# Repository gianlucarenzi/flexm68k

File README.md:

# flexm68k

This is a Proof Of Concept to relocate anywhere in the motherboard of an Amiga500 the CPU.
It consists of two PCB Adapter for Original Primary CPU Socket Adapter + a 64pin FFC/FPC cable and a Secondary CPU Socket Adapter with the add of power supply (as seen in the Molex Floppy Header Power Cable)

Will it work?? ;-P

Gianluca

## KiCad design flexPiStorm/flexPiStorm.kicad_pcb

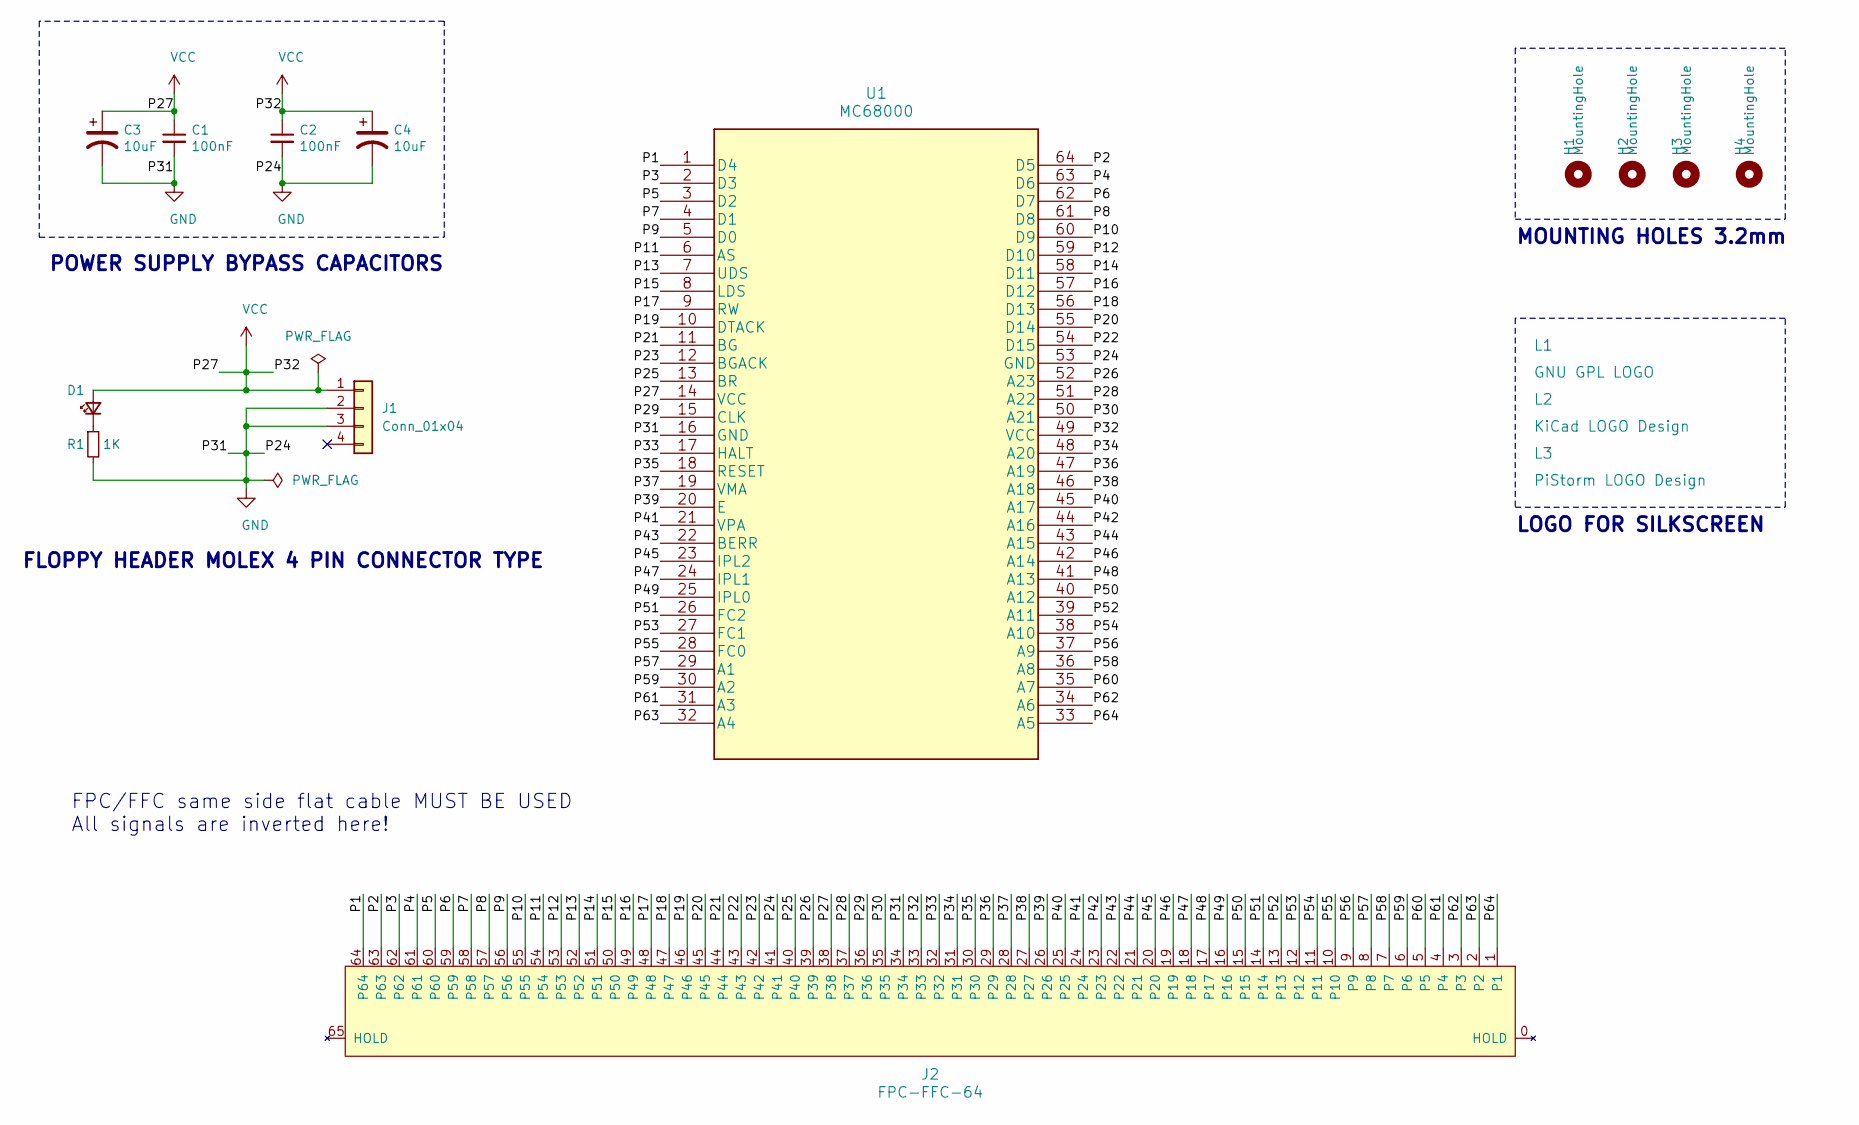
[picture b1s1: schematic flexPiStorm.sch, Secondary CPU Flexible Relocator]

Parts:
C1, C2: 100nF; C_1206_3216Metric_Pad1.33x1.80mm_HandSolder
C3, C4: 10uF; CP_EIA-3216-12_Kemet-S_Pad1.58x1.35mm_HandSolder
D1: LED_Small; LED_1206_3216Metric_Pad1.42x1.75mm_HandSolder
H1, H2, H3, H4: MountingHole; MountingHole_3.2mm_M3
J1: Conn_01x04; PinHeader_1x04_P2.54mm_Horizontal
J2: FPC-FFC-64; FPC_64
L1: GNU GPL LOGO; Symbol_GNU-GPL_SilkScreen_Small
L2: KiCad LOGO Design; KiCad-Logo2_6mm_SilkScreen
L3: PiStorm LOGO Design; PiStorm_32x6-NEG
R1: 1K; R_1206_3216Metric_Pad1.30x1.75mm_HandSolder
U1: MC68000; MC68000-SOCKET-RELOCATOR_FEMALE

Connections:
/P1: J2.64, U1.1 (D4)
/P2: J2.63, U1.64 (D5)
/P3: J2.62, U1.2 (D3)
/P4: J2.61, U1.63 (D6)
/P5: J2.60, U1.3 (D2)
/P6: J2.59, U1.62 (D7)
/P7: J2.58, U1.4 (D1)
/P8: J2.57, U1.61 (D8)
/P9: J2.56, U1.5 (D0)
/P10: J2.55, U1.60 (D9)
/P11: J2.54, U1.6 (AS)
/P12: J2.53, U1.59 (D10)
/P13: J2.52, U1.7 (UDS)
/P14: J2.51, U1.58 (D11)
/P15: J2.50, U1.8 (LDS)
/P16: J2.49, U1.57 (D12)
/P17: J2.48, U1.9 (RW)
/P18: J2.47, U1.56 (D13)
/P19: J2.46, U1.10 (DTACK)
/P20: J2.45, U1.55 (D14)
/P21: J2.44, U1.11 (BG)
/P22: J2.43, U1.54 (D15)
/P23: J2.42, U1.12 (BGACK)
/P25: J2.40, U1.13 (BR)
/P26: J2.39, U1.52 (A23)
/P28: J2.37, U1.51 (A22)
/P29: J2.36, U1.15 (CLK)
/P30: J2.35, U1.50 (A21)
/P33: J2.32, U1.17 (HALT)
/P34: J2.31, U1.48 (A20)
/P35: J2.30, U1.18 (RESET)
/P36: J2.29, U1.47 (A19)
/P37: J2.28, U1.19 (VMA)
/P38: J2.27, U1.46 (A18)
/P39: J2.26, U1.20 (E)
/P40: J2.25, U1.45 (A17)
/P41: J2.24, U1.21 (VPA)
/P42: J2.23, U1.44 (A16)
/P43: J2.22, U1.22 (BERR)
/P44: J2.21, U1.43 (A15)
/P45: J2.20, U1.23 (IPL2)
/P46: J2.19, U1.42 (A14)
/P47: J2.18, U1.24 (IPL1)
/P48: J2.17, U1.41 (A13)
/P49: J2.16, U1.25 (IPL0)
/P50: J2.15, U1.40 (A12)
/P51: J2.14, U1.26 (FC2)
/P52: J2.13, U1.39 (A11)
/P53: J2.12, U1.27 (FC1)
/P54: J2.11, U1.38 (A10)
/P55: J2.10, U1.28 (FC0)
/P56: J2.9, U1.37 (A9)
/P57: J2.8, U1.29 (A1)
/P58: J2.7, U1.36 (A8)
/P59: J2.6, U1.30 (A2)
/P60: J2.5, U1.35 (A7)
/P61: J2.4, U1.31 (A3)
/P62: J2.3, U1.34 (A6)
/P63: J2.2, U1.32 (A4)
/P64: J2.1, U1.33 (A5)
GND: C1.2, C2.2, C3.2, C4.2, J1.2, J1.3, J2.34, J2.41, R1.2, U1.16 (GND), U1.53 (GND)
unnamed: D1.1 (K), R1.1
VCC: C1.1, C2.1, C3.1, C4.1, D1.2 (A), J1.1, J2.33, J2.38, U1.14 (VCC), U1.49 (VCC)

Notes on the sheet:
MOUNTING HOLES 3.2mm
LOGO FOR SILKSCREEN
FLOPPY HEADER MOLEX 4 PIN CONNECTOR TYPE
POWER SUPPLY BYPASS CAPACITORS
FPC/FFC same side flat cable MUST BE USED All signals are inverted here!

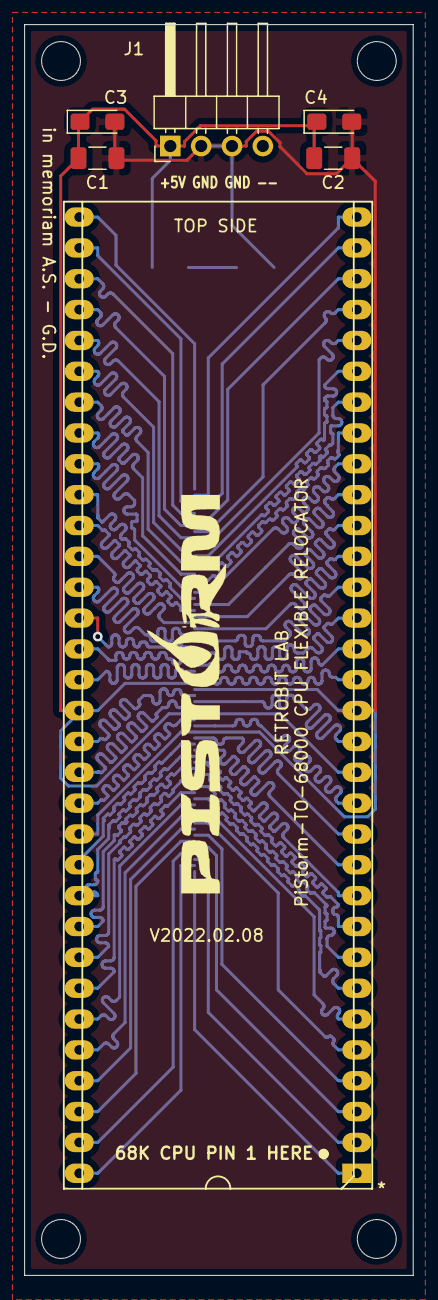
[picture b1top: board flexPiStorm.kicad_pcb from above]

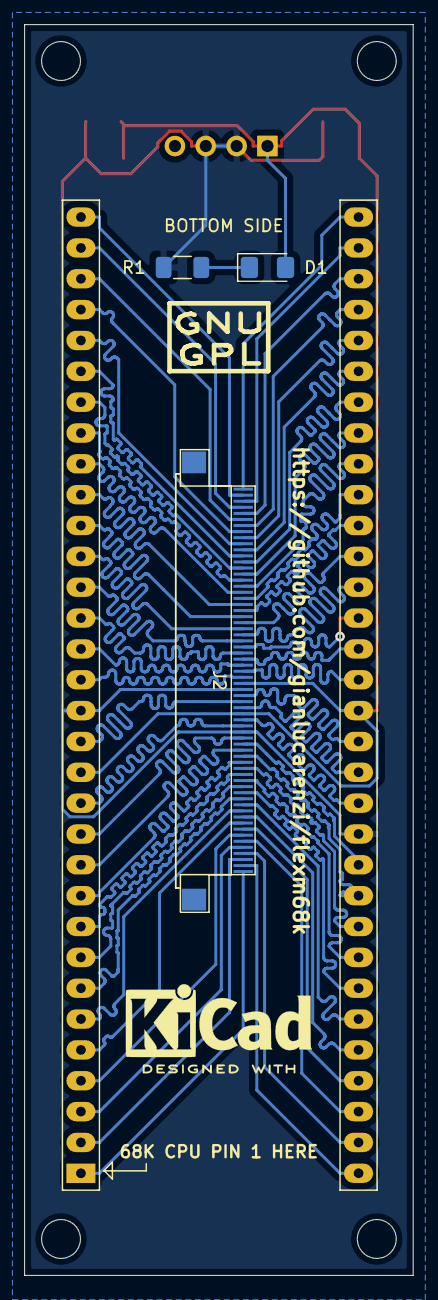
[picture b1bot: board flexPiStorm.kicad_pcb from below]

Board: 2 copper layers, 32.0 x 103.0 mm, 16 parts (5 on the bottom side), 63 nets.

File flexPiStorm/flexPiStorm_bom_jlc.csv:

"Comment","Designator","Footprint","LCSC Part #"
"MC68000","U1","",""
"Conn_01x04","J1","",""
"PiStorm LOGO Design","L3","",""
"100nF","C1 C2","",""
"10uF","C3 C4","",""
"FPC-FFC-64","J2","",""
"LED_Small","D1","",""
"1K","R1","",""
"GNU GPL LOGO","L1","",""
"KiCad LOGO Design","L2","",""

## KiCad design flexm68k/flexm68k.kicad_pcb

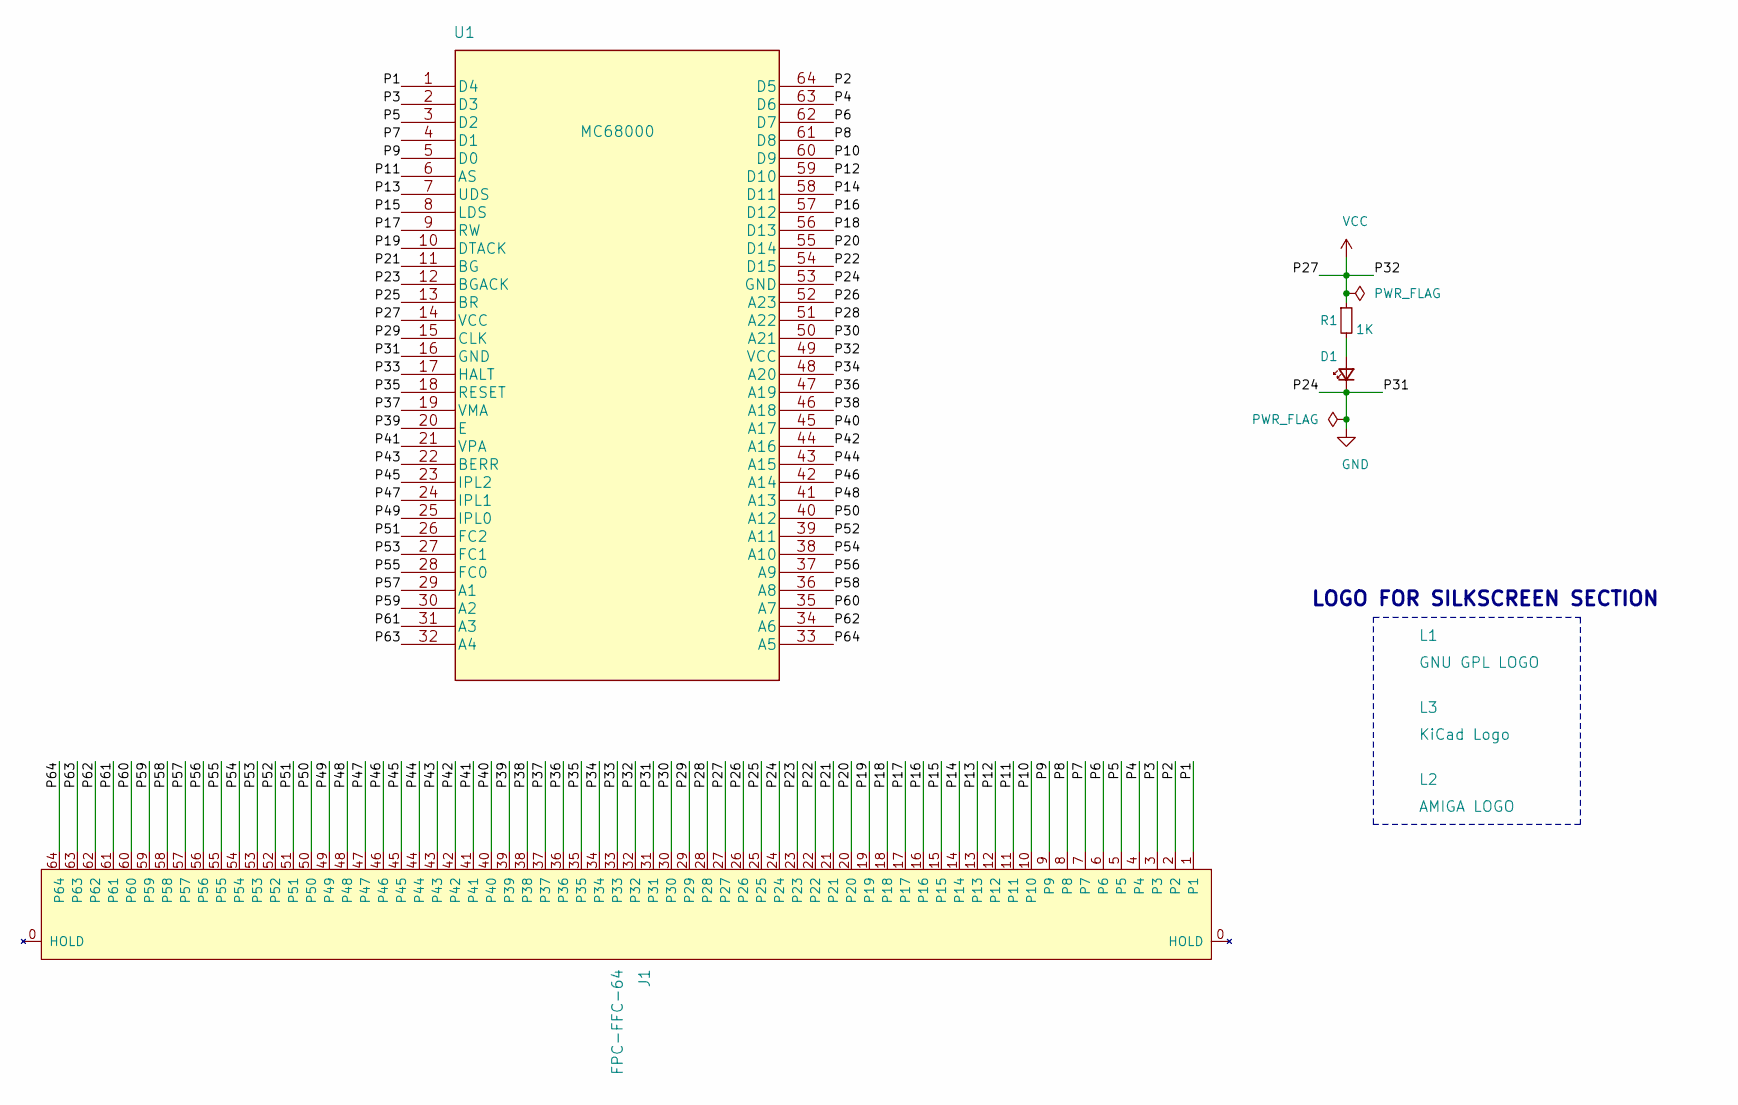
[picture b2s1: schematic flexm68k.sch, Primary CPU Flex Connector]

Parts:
D1: LED_Small; LED_1206_3216Metric_Pad1.42x1.75mm_HandSolder
J1: FPC-FFC-64; FPC_64
L1: GNU GPL LOGO; Symbol_GNU-GPL_SilkScreen_Small
L2: AMIGA LOGO; amigaLogo_BW_31x12mm
L3: KiCad Logo; KiCad-Logo2_6mm_SilkScreen
R1: 1K; R_1206_3216Metric_Pad1.30x1.75mm_HandSolder
U1: MC68000; MC68000-RELOCATOR-MALE

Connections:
/P1: J1.1, U1.1 (D4)
/P2: J1.2, U1.64 (D5)
/P3: J1.3, U1.2 (D3)
/P4: J1.4, U1.63 (D6)
/P5: J1.5, U1.3 (D2)
/P6: J1.6, U1.62 (D7)
/P7: J1.7, U1.4 (D1)
/P8: J1.8, U1.61 (D8)
/P9: J1.9, U1.5 (D0)
/P10: J1.10, U1.60 (D9)
/P11: J1.11, U1.6 (AS)
/P12: J1.12, U1.59 (D10)
/P13: J1.13, U1.7 (UDS)
/P14: J1.14, U1.58 (D11)
/P15: J1.15, U1.8 (LDS)
/P16: J1.16, U1.57 (D12)
/P17: J1.17, U1.9 (RW)
/P18: J1.18, U1.56 (D13)
/P19: J1.19, U1.10 (DTACK)
/P20: J1.20, U1.55 (D14)
/P21: J1.21, U1.11 (BG)
/P22: J1.22, U1.54 (D15)
/P23: J1.23, U1.12 (BGACK)
/P25: J1.25, U1.13 (BR)
/P26: J1.26, U1.52 (A23)
/P28: J1.28, U1.51 (A22)
/P29: J1.29, U1.15 (CLK)
/P30: J1.30, U1.50 (A21)
/P33: J1.33, U1.17 (HALT)
/P34: J1.34, U1.48 (A20)
/P35: J1.35, U1.18 (RESET)
/P36: J1.36, U1.47 (A19)
/P37: J1.37, U1.19 (VMA)
/P38: J1.38, U1.46 (A18)
/P39: J1.39, U1.20 (E)
/P40: J1.40, U1.45 (A17)
/P41: J1.41, U1.21 (VPA)
/P42: J1.42, U1.44 (A16)
/P43: J1.43, U1.22 (BERR)
/P44: J1.44, U1.43 (A15)
/P45: J1.45, U1.23 (IPL2)
/P46: J1.46, U1.42 (A14)
/P47: J1.47, U1.24 (IPL1)
/P48: J1.48, U1.41 (A13)
/P49: J1.49, U1.25 (IPL0)
/P50: J1.50, U1.40 (A12)
/P51: J1.51, U1.26 (FC2)
/P52: J1.52, U1.39 (A11)
/P53: J1.53, U1.27 (FC1)
/P54: J1.54, U1.38 (A10)
/P55: J1.55, U1.28 (FC0)
/P56: J1.56, U1.37 (A9)
/P57: J1.57, U1.29 (A1)
/P58: J1.58, U1.36 (A8)
/P59: J1.59, U1.30 (A2)
/P60: J1.60, U1.35 (A7)
/P61: J1.61, U1.31 (A3)
/P62: J1.62, U1.34 (A6)
/P63: J1.63, U1.32 (A4)
/P64: J1.64, U1.33 (A5)
GND: D1.1 (K), J1.24, J1.31, U1.16 (GND), U1.53 (GND)
unnamed: D1.2 (A), R1.2
VCC: J1.27, J1.32, R1.1, U1.14 (VCC), U1.49 (VCC)

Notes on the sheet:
LOGO FOR SILKSCREEN SECTION

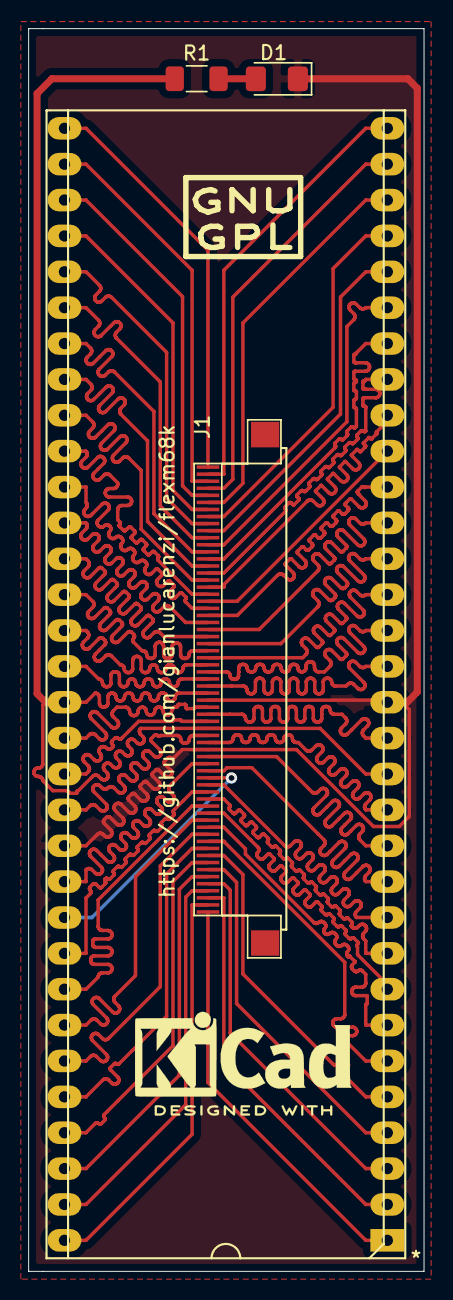
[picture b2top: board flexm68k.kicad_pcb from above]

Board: 2 copper layers, 28.0 x 88.0 mm, 7 parts (1 on the bottom side), 63 nets.

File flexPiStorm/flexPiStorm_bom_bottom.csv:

"FPC-FFC-64","J2","",""
"LED_Small","D1","",""
"1K","R1","",""
"GNU GPL LOGO","L1","",""
"KiCad LOGO Design","L2","",""

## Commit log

2021-06-25 First import
2021-06-25 Schematics
2021-06-25 LED and RESISTOR added
2021-06-25 New flexPiStorm
2021-06-27 Added LOGOs in the schematics, so the PCB will have them already. Run DRC for errors. Report only three (3) overlap for silkscreen and filled zones. No problem at all.
2021-06-28 Added bypass capacitors 10000pF Ceramics 1206 HandSolder
2021-06-29 Added a better filter for powersupply TANTALUM + CERAMIC (x2)
2021-06-29 Sent to JLCPCB 29 Jun 2021
2021-06-29 FFC/FPC Flex Cables from AliExpress FFC/FPC Connectors 64PIN 0.5mm from Farnell Other components provided by Eurek SRL
2021-08-08 Wrong footprint for CPU. Now should be corrected
2021-08-08 REMOVED. May be is not needed. I'll see.
2021-08-08 Modified for correct footprint CPU
2021-08-08 Removed
2022-01-26 Added as last run
2022-01-26 Inverted ffc/fpc pinout for reverse mounting. Cable must be SAME SIDE
2022-01-26 interactive bom
2022-02-08 Modified as requested by JLCPCB with e-mail in beginning of Feb. 2022 (Tracks too small)
2022-02-08 Added for future usage for JLCPCB
